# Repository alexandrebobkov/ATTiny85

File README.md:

<h2>ATTiny85 Inside</h2>

<div><p><i>A customizable I2C peripheral slave device powered by ATTiny85 controller. Build your own I2C device.</i></p></div>

<div><p>An eco-system of ESP32 and ATTiny85 microcontrollers. ESP32 serves a function of I2C master device, primarily for demonstration purposes. ATTiny85 serves a function of I2C slave device, i.e. peripheral.</p><p>Source code for ATTiny85 microcontrollers is written using Arduino C++ framework.</p></div>

<h3>Pins Reservations</h3>
<p>
 <li>PB3 - Status LED</li>
 <li>PB4 - Sensor</li>
 <li>PB0 - I2C SDA</li>
 <li>PB2 - I2C SCL</li>
</p>
<h3>Operations Codes</h3>
<li>0x10: LED high pulse</li>
<li>0x11: LED low pulse</li>
<li>0x12: LED steady</li>

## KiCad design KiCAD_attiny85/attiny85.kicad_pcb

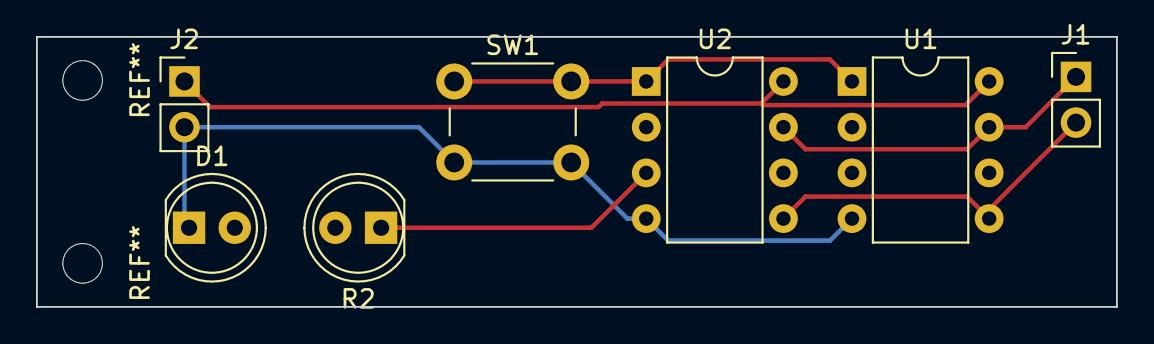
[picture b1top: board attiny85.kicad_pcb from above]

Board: 2 copper layers, 60.0 x 15.0 mm, 7 parts (0 on the bottom side), 6 nets.

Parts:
D1: LED; LED_D5.0mm
J1: I2C_Conn_01x02_Pin; PinHeader_1x02_P2.54mm_Vertical
J2: PWR_Conn_01x02_Pin; PinHeader_1x02_P2.54mm_Vertical
R2: R_Photo; LED_D5.0mm
SW1: RESET; SW_PUSH_6mm_H5mm
U1, U2: ATtiny85-8P; DIP-8_W7.62mm

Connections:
GND: D1.1 (K), J2.2, SW1.2, U1.4 (GND), U2.4 (GND)
unnamed: J1.1, U1.7 (D2(A1)/SCL/SCK/PB2), U2.7 (D2(A1)/SCL/SCK/PB2)
unnamed: J1.2, U1.5 (D0/MOSI/SDA/PB0), U2.5 (D0/MOSI/SDA/PB0)
unnamed: SW1.1, U1.1 (D5(A0)/ADC0/PB5/~RESET), U2.1 (D5(A0)/ADC0/PB5/~RESET)
unnamed: R2.1, U2.3 (D4(A2)/ADC2/PB4)
VCC: J2.1, U1.8 (VCC), U2.8 (VCC)

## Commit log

2023-12-01 Breathing LED cycle
2023-12-03 Nano 2040 Connect & ATTiny85 I2C
2023-12-11 comments
2023-12-11 i2c sensor
2023-12-11 debugging
2023-12-12 updated library
2023-12-12 sensors values Struct
2023-12-14 light sensor
2023-12-14 KiCAD
2023-12-18 I2C bus scan for devices
2023-12-20 toggle LCD backlight
2023-12-23 included required libraries locally
2023-12-23 I2C receive() and request() handlers
2023-12-24 esp32 s2 mini
2023-12-25 I2C scan
2023-12-25 LCD output
2023-12-27 I2C communication
2023-12-27 registers
2024-01-07 i2c basic
